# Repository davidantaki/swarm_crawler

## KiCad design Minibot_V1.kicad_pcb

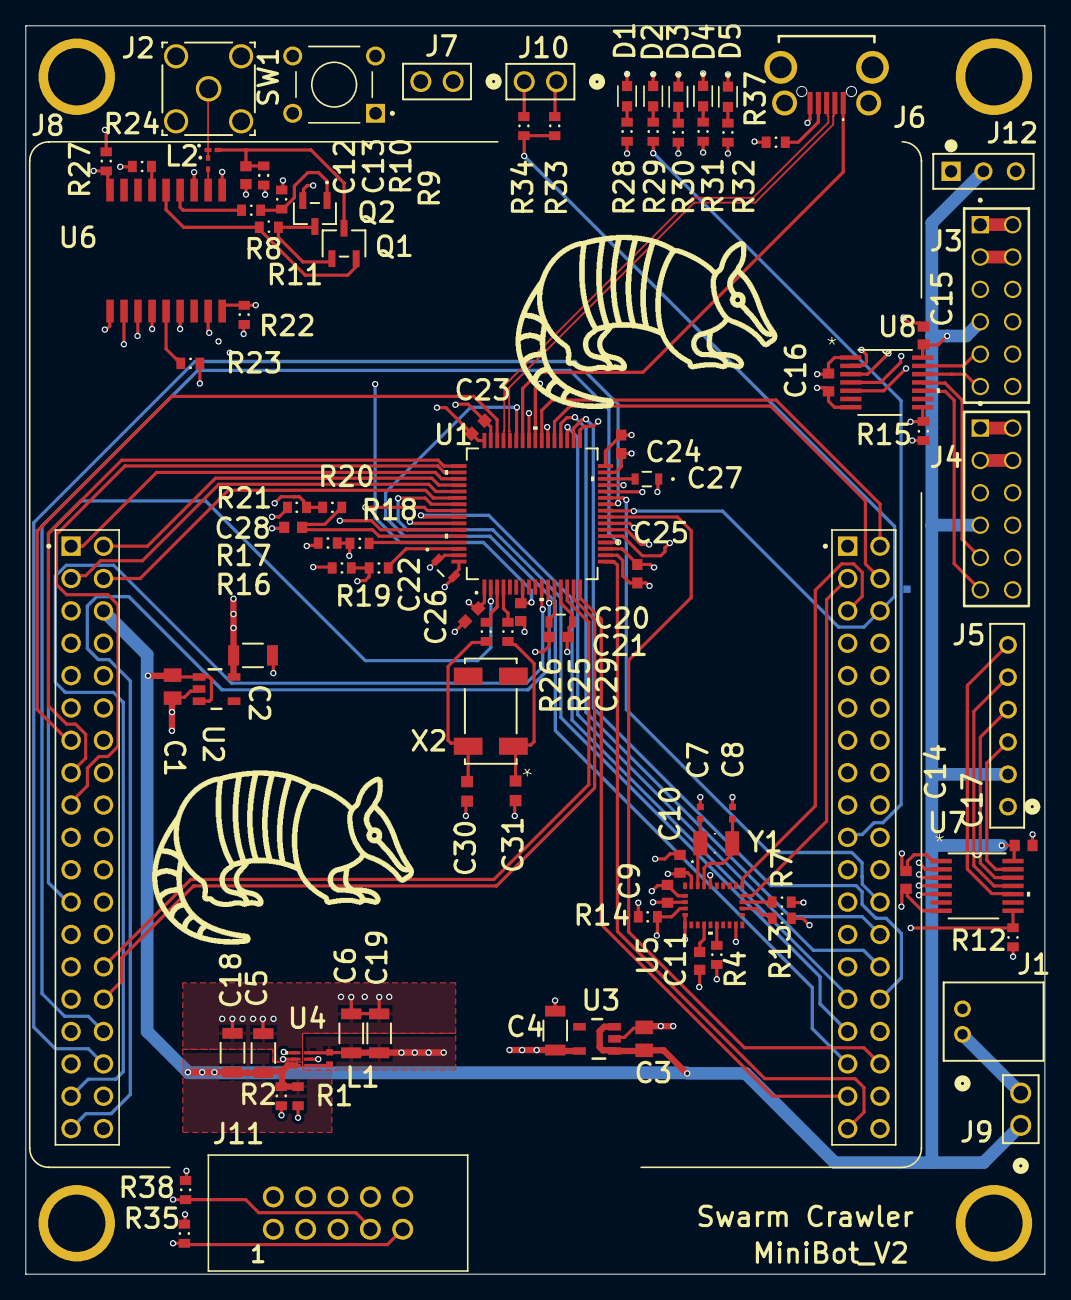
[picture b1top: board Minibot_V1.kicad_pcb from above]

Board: 6 copper layers, 80.0 x 98.0 mm, 97 parts (0 on the bottom side), 97 nets.

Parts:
C1, C3: GRM21BR71C475KE51L; CAP_GRM0805_2X1P25_MUR
C2, C4, C5, C6: CL31B106KOHNNWE; CAP_CL31_SAM
C7, C8: CBR04C220F5GAC; CAPC10555_55N_KEM
C9, C10, C11, C13, C14, C15, C16, C17: 0603; 1608[0603]
C12: C0603C0G1E270J030BA; CAP_0603_TDK
C18, C19: no stuff; CAP_CL31_SAM
C20: C1608X5R1C105K080AA; CAP_1608_TDK
C21, C23, C24, C25, C26: CC0603KRX7R7BB104; CC0603N_YAG
C22: C1608X5R1C475K080AC; CAP_1608_TDK
C27: C1608X5R1C225K080AB; CAP_1608_TDK
C28, C29: Cap Semi; 1608[0603]
C30, C31: GRM1885C1H4R3BA01D; CAPC1608X90N
D1, D2, D3, D4, D5: 150060SS75000; LED_150060SS75000
J1: S2B-PH-K-S(LF)(SN); CONN_S2B-PH-K-S_JST
J2: RF2-04A-T-00-50-G; CONN_RF2-04A-T-00-50-G_ADM
J3, J4: TSW-106-07-F-D; SAMTEC_TSW-106-07-F-D
J5: TSW-106-14-F-S; CON6_1X6_TU_TSW
J6: MCR-B-S-RA-SMT-CS14-T_R; MCRBSRASMTCS14TR
J7, J9, J10: 61300211121; CONN_61300211121_WRE
J8: NUCLEO-F446RE; MODULE_NUCLEO-F446RE
J11: 61201021621
J12: 22284036; 22-28-4036_MOL
L1: 1239AS-H-1R0M=P2; CAPC10555_55N_KEM
L2: MLG0603S36NJT000; IND_0603_TDK
Q1: AO3407A; SOT-23-3L_AOS
Q2: SMMBT3904LT1G; SOT-23-3_1P4X3P040_ONS
R1, R2, R4, R7, R8, R9, R10, R11, R12, R13, R14, R15, R16, R17, R18, R19, R20, R21, R27: 0603; J1-0603
R22, R23, R24, R25, R26, R28, R29, R30, R31, R32, R33, R34, R35, R37, R38: Res3; J1-0603
SW1: 1825910-2; TE_1825910-2
U1: STM32F446RCT6TR; LQFP64-10x10mm
U2, U3: LP2981-33DBVR; DBV0005A_N
U4: MP2148GQD-33-Z; QFN-1p0x1p5_MNP
U5: BNO055; QFN_BNO055_BOS
U6: GPS_FN; SL871
U7, U8: TXB0104PWR; PW14
X2: ABS25-32.768KHZ-1-T; ABS25-32.768KHZ-1-T_ABR
Y1: ECS-.327-12.5-34B-C-TR; XTAL_ECS-.327-12.5-34B-C-TR

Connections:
1PPS_GPS: J8.CN7_3, U1.53, U6.4
3V3: C6.2, C14.2, C16.2, C19.2, C20.2, C21.2, C22.2, C23.2, C24.2, C25.2, C26.2, J11.10, L1.2, R16.2, R17.2, R21.2, R35.2, U1.1, U1.13, U1.19, U1.32, U1.48, U1.64, U4.6, U7.1, U8.1
3V3_GPS: C2.2, R22.2, R24.1, U2.5, U6.6, U6.8
3V3_IMU: C4.2, C9.2, C10.2, R4.2, R14.2, U3.5, U5.3, U5.28
5V: C1.2, C3.2, C5.2, C15.2, C17.2, C18.2, J3.07, J4.07, J5.2, J8.CN7_6, J9.1, J12.A2, R1.2, R2.1, U2.1, U2.3, U3.1, U3.3, U4.3, U7.14, U8.14
ANT: C12.1, J2.1, L2.1
BATT_VIN: J10.1, R33.1
BATT_VOL: J8.CN10_6, R33.2, R34.1, U1.25
BOOT_IMU: J8.CN10_22, R14.1, U1.28, U5.4
D_N: J6.2, U1.44
D_P: J6.3, U1.45
ENC_1_A_5V: J3.09, U8.13
ENC_1_B_5V: J3.11, U8.12
ENC_2_A_5V: J4.09, U8.11
ENC_2_B_5V: J4.11, U8.10
FORCE_ON_N: J8.CN7_4, R27.2, U1.54, U6.18
GND: C1.1, C2.1, C3.1, C4.1, C5.1, C6.1, C7.2, C8.2, C9.1, C10.1, C11.1, C13.1, C14.1, C15.1, C16.1, C17.1, C18.1, C19.1, C20.1, C21.1, C22.1, C23.1, C24.1, C25.1, C26.1, C27.1, C28.1, C29.1, C30.2, C31.2, D1.1, D2.1, D3.1, D4.1, D5.1, J1.2, J2.2, J2.3, J2.4, J2.5, J3.05, J4.05, J5.1, J6.5, J6.MH1, J6.MH2, J6.MH3, J6.MH4, J7.2, J8.CN7_8, J8.CN7_19, J8.CN7_20, J8.CN7_22, J8.CN10_9, J8.CN10_20, J10.2, J11.2, J11.6, J11.8, J12.A3, Q2.2, R7.1, R9.1, R10.1, R12.1, R13.1, R15.1, R23.1, R27.1, R34.2, R37.1, R38.1, SW1.3, U1.12, U1.18, U1.31, U1.47, U1.63, U2.2, U3.2, U4.2, U5.2, U5.5, U5.6, U5.25, U6.1, U6.10, U6.12, U7.7, U8.7
I2C1_SCL_IMU: J8.CN10_3, R17.1, R18.2, U5.19
I2C1_SDA_IMU: J8.CN10_5, R16.1, R19.2, U5.20
ID: J6.4, R37.2
INT_IMU: J8.CN10_23, U1.41, U5.14
LED_1: J8.CN10_1, R28.1, U1.40
LED_2: J8.CN10_19, R29.1, U1.38
LED_3: J8.CN10_2, R30.1, U1.39
LED_4: J8.CN10_4, R31.1, U1.37
LED_5: J8.CN10_16, R32.1, U1.33
MOTOR_1_N: J3.03, J3.04
MOTOR_1_P: J3.01, J3.02
MOTOR_2_N: J4.03, J4.04
MOTOR_2_P: J4.01, J4.02
MOTOR_IN1: J5.3, U7.13
MOTOR_IN2: J5.4, U7.12
MOTOR_IN3: J5.5, U7.11
MOTOR_IN4: J5.6, U7.10
MOT_1A_3V3: J8.CN10_13, U1.22, U7.2
MOT_1B_3V3: J8.CN10_15, U1.23, U7.3
MOT_2A_3V3: J8.CN10_17, U1.58, U7.4
MOT_2B_3V3: J8.CN7_21, U1.59, U7.5
NRST: C29.2, SW1.1, U1.7
NetC7_1: C7.1, U5.27, Y1.2
NetC8_1: C8.1, U5.26, Y1.1
NetC11_2: C11.2, U5.9
NetC12_2: C12.2, U6.11
NetC13_2: C13.2, L2.2, Q1.3, R10.2
NetC27_2: C27.2, U1.30
NetC28_2: C28.2, R20.2, U1.60
NetC30_1: C30.1, R26.2, X2.4
NetC31_1: C31.1, R25.2, X2.1
NetD1_2: D1.2, R28.2
NetD2_2: D2.2, R29.2
NetD3_2: D3.2, R30.2
NetD4_2: D4.2, R31.2
NetD5_2: D5.2, R32.2
NetJ1_1: J1.1, J9.2
NetJ7_1: J7.1, R20.1, R21.1
NetL1_1: L1.1, U4.4
NetQ1_1: Q1.1, Q2.3, R11.1
NetQ1_2: Q1.2, R11.2, U6.14
NetQ2_1: Q2.1, R8.1, R9.2
NetR4_1: R4.1, U5.11
NetR7_2: R7.2, U5.18
NetR8_2: R8.2, U6.13
NetR18_1: R18.1, U1.61
NetR19_1: R19.1, U1.62
NetR23_2: R23.2, U6.5
NetR24_2: R24.2, U6.15
NetR25_1: R25.1, U1.4
NetR26_1: R26.1, U1.3
OE_ENC: J8.CN10_29, R15.2, U1.57, U8.8
OE_MOT: J8.CN10_27, R12.2, U1.56, U7.8
PA2: J8.CN10_35, U1.16
PA3: J8.CN10_37, U1.17
PA4: J8.CN7_32, U1.20
PB0: J8.CN7_34, U1.26
PB1: J8.CN10_24, U1.27
PB10: J8.CN10_25, U1.29
PB13: J8.CN10_30, U1.34
PB14: J8.CN10_28, U1.35
PB15: J8.CN10_26, U1.36
PC2: J8.CN7_35, U1.10
PC3: J8.CN7_37, U1.11
PC4: J8.CN10_34, U1.24
PC13: J8.CN7_23, U1.2
PG: R2.2, U4.1
RESET_N_GPS: J8.CN7_17, R22.1, U1.50, U6.9
SERVO_PWM: J8.CN10_33, J12.A1, U1.43
SWCLK: J8.CN7_15, J11.7, R38.2, U1.49
SWDIO: J8.CN7_13, J11.9, R35.1, U1.46
SW_REG_EN: R1.1, U4.5
S_ADDR_IMU: R13.2, U5.17
TIM2_CH1_ENC_1A: J8.CN10_11, U1.21, U8.2
TIM2_CH2_ENC_1B: J8.CN10_31, U1.55, U8.3
TIM5_CH1_ENC_2A: J8.CN7_28, U1.14, U8.4
TIM5_CH2_ENC_2B: J8.CN7_30, U1.15, U8.5
UART3_RX_GPS: J8.CN7_1, U1.51, U6.3
UART3_TX_GPS: J8.CN7_2, U1.52, U6.2
VBUS: J6.1, U1.42

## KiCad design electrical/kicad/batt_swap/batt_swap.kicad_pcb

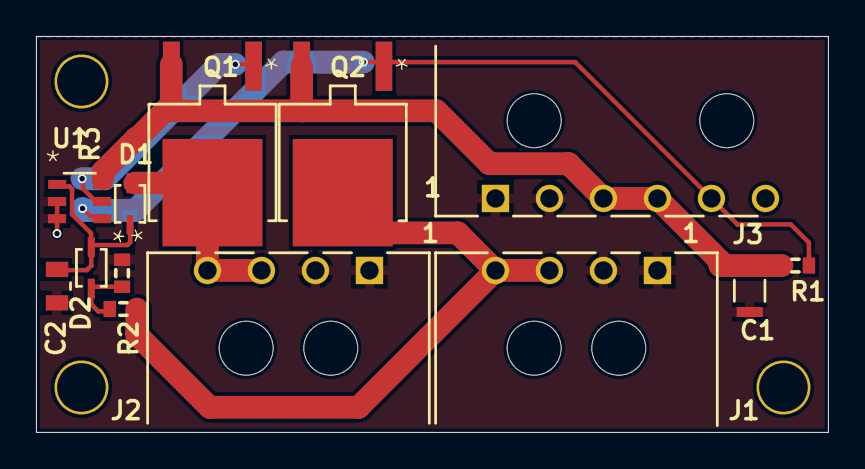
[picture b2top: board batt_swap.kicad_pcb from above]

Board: 2 copper layers, 44.0 x 22.0 mm, 13 parts (0 on the bottom side), 8 nets.

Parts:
C1: C2012JB1V226M125AC; CAP_2012_TDK
C2: CL21B105KBFNNNE; CAP_CL21_SAM
D1, D2: SD103AWS-7-F; SOD323_DIO
J1, J2: 436500400; CON_436500400_MOL
J3: 436500600; CON_436500600_MOL
Q1, Q2: AOD407; TO252_AOS
R1, R2, R3: Res3; J1-0603
U1: LTC4412ES6#TRPBF; LTC4412ES6#TRPBF_ADI

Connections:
GND: C1.1, C2.1, J1.1, J1.2, J2.1, J2.2, J3.1, J3.2, R3.1, U1.2, U1.3
NetC2_2: C2.2, D1.1, D2.1, U1.1
NetD2_2: D2.2, R2.1, R3.2
NetQ1_1: Q1.1, U1.5
batt: D1.2, J2.3, J2.4, Q1.3
hub: J1.3, J1.4, Q2.3, R2.2
stat: J3.5, Q2.1, R1.1, U1.4
vout: C1.2, J3.3, J3.4, Q1.2, Q2.2, R1.2, U1.6

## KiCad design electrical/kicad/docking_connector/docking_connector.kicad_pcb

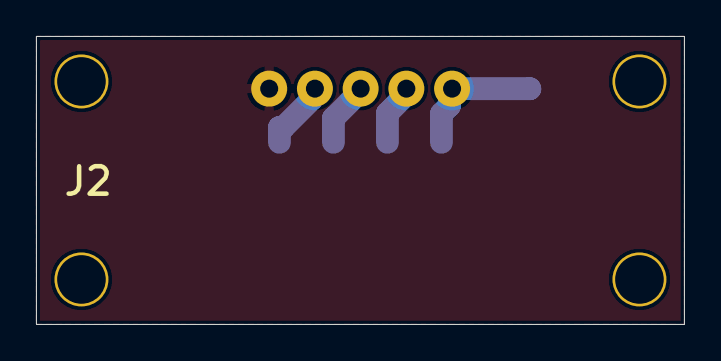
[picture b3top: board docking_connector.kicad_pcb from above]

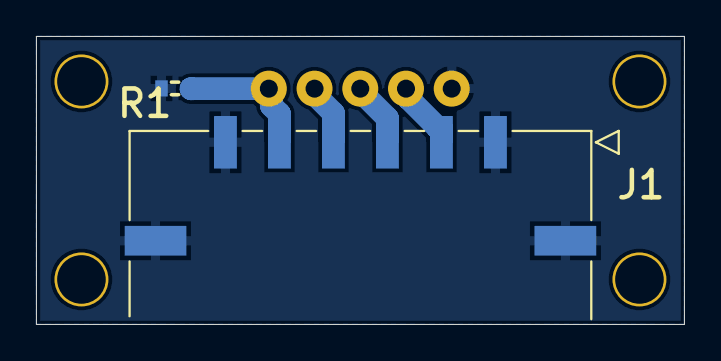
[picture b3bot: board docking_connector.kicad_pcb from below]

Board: 2 copper layers, 36.0 x 16.0 mm, 3 parts (2 on the bottom side), 5 nets.

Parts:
J1: 436500612; CON_436500612
J2: 5413
R1: Res3; J1-0603

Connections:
GND: J1.1, J1.6, J1.P1, J1.P2, J2.1, R1.1
NetJ1_2: J1.2, J2.2
NetJ1_3: J1.3, J2.3
NetJ1_4: J1.4, J2.4
NetJ1_5: J1.5, J2.5, R1.2

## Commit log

2024-02-29 Create temp
2024-02-29 Create tempy
2024-02-29 Rename Minibot_V1.pdf to Minibot_V1_Schematic.pdf
